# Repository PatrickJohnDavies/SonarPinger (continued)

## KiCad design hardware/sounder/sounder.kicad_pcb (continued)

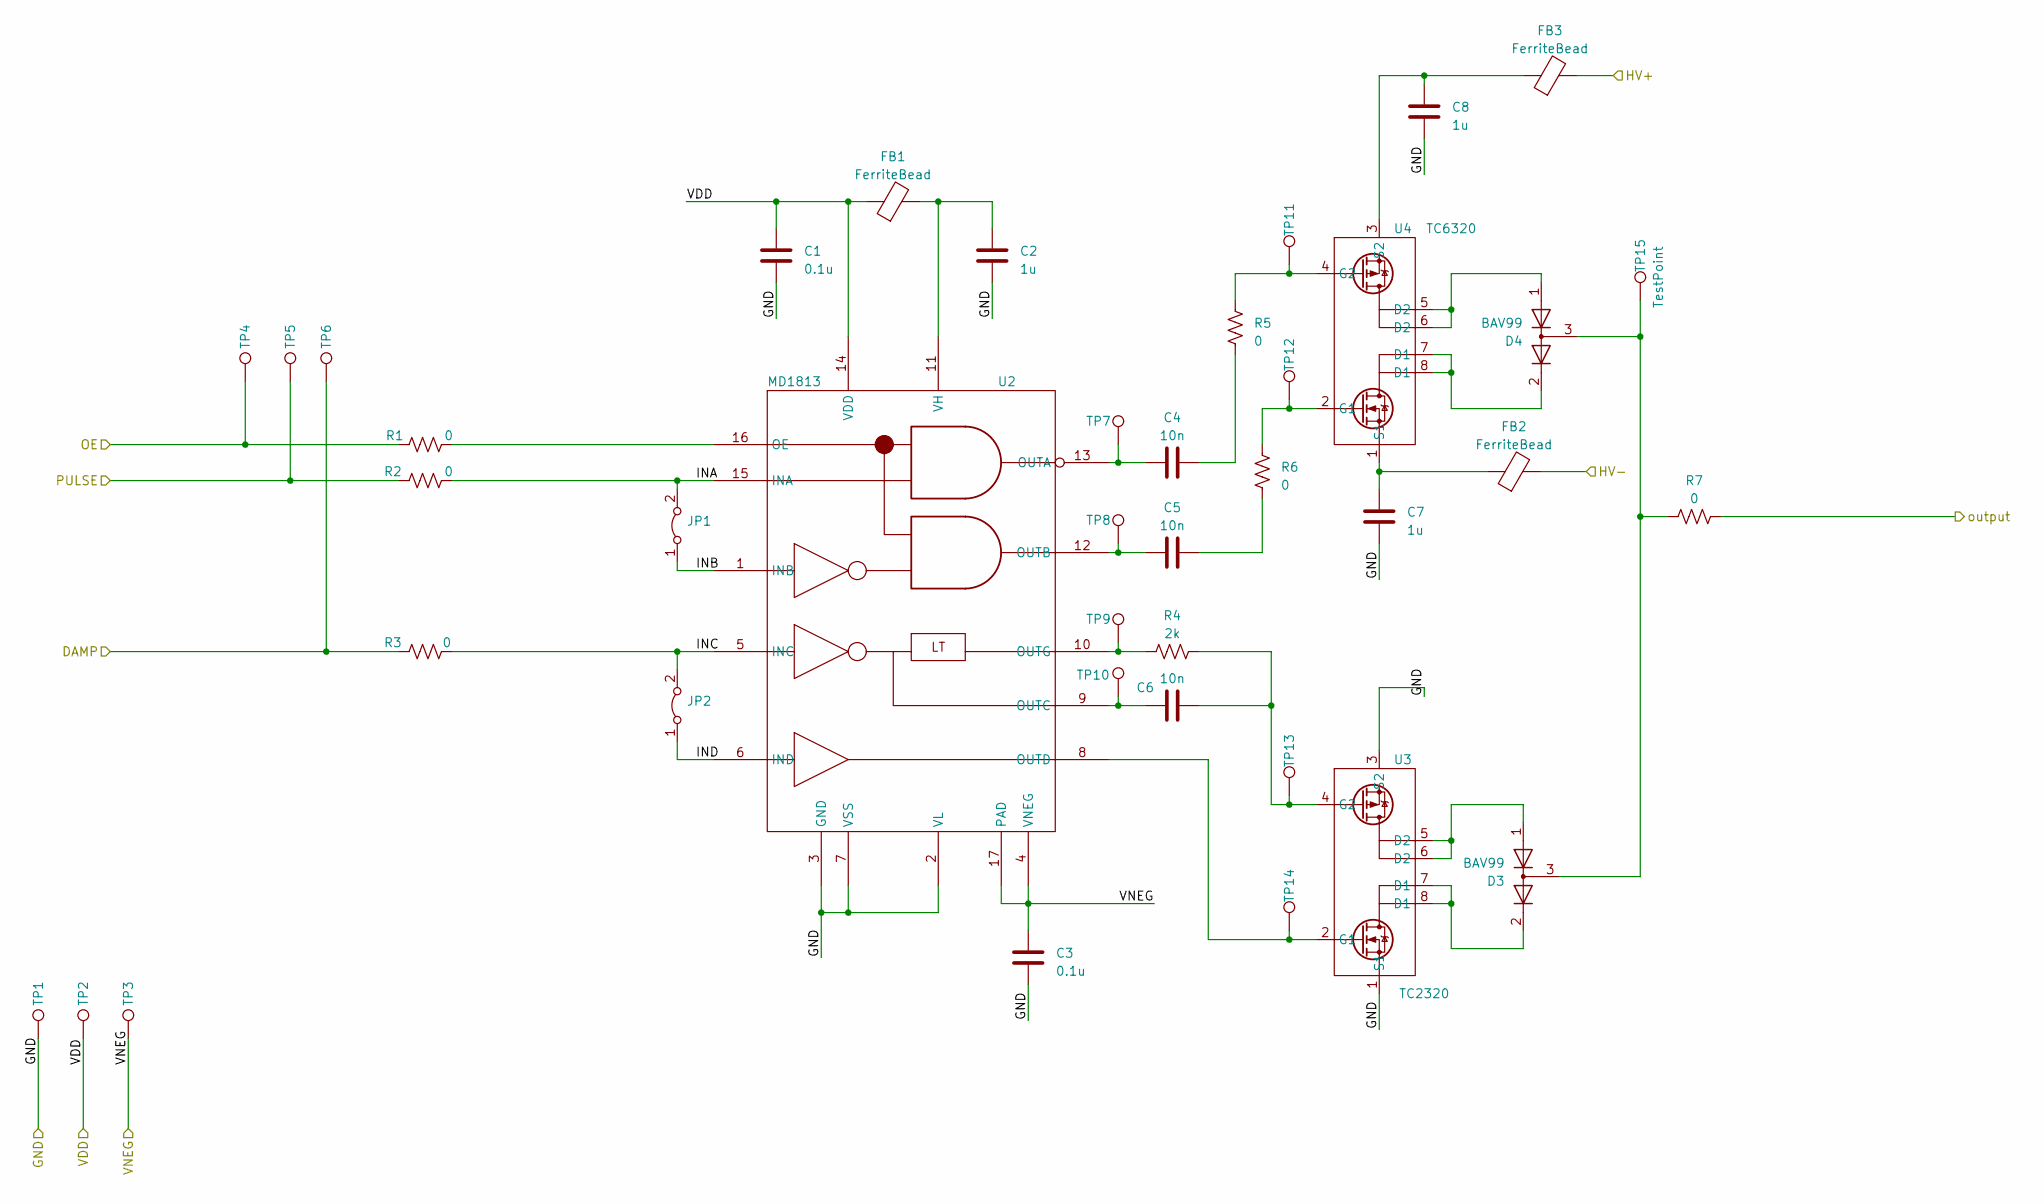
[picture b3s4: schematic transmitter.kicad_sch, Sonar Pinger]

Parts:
C1, C3: 0.1u; C_0603_1608Metric
C2: 1u; C_0201_0603Metric
C4, C5, C6: 10n; C_0603_1608Metric
C7, C8: 1u; C_1812_4532Metric
D3, D4: BAV99; SOT-23
FB1, FB2, FB3: FerriteBead; L_0603_1608Metric
JP1, JP2: Jumper_2_Bridged; SolderJumper-2_P1.3mm_Bridged_RoundedPad1.0x1.5mm
R1, R2, R3, R5, R6, R7: 0; R_0603_1608Metric
R4: 2k; R_0603_1608Metric
TP1, TP2, TP3, TP4, TP5, TP6, TP7, TP8, TP9, TP10, TP11, TP12, TP13, TP14, TP15: TestPoint; TestPoint_THTPad_D1.8mm_Drill1.2mm
U2: MD1813; QFN-16-1EP_4x4mm_P0.65mm_EP2.5x2.5mm
U3: TC2320; SOIC-8_3.9x4.9mm_P1.27mm
U4: TC6320; SOIC-8_3.9x4.9mm_P1.27mm

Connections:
/9V: C1.2, FB1.1, TP2.1, U2.14 (VDD); also elsewhere on the board
/100V: FB3.2; also elsewhere on the board
/-9V: C3.2, TP3.1, U2.4 (VNEG), U2.17 (PAD); also elsewhere on the board
/-100V: FB2.2; also elsewhere on the board
/DAMP: R3.1, TP6.1; also elsewhere on the board
/OE: R1.1, TP4.1; also elsewhere on the board
/PULSE: R2.1, TP5.1; also elsewhere on the board
/receiver/input: R7.2; also elsewhere on the board
/transmitter/INA: JP1.2 (B), R2.2, U2.15 (INA)
/transmitter/INB: JP1.1 (A), U2.1 (INB)
/transmitter/INC: JP2.2 (B), R3.2, U2.5 (INC)
/transmitter/IND: JP2.1 (A), U2.6 (IND)
GND: C1.1, C2.1, C3.1, C7.1, C8.1, TP1.1, U2.2 (VL), U2.3 (GND), U2.7 (VSS), U3.1 (S1), U3.3 (S2); also elsewhere on the board
unnamed: C4.2, R5.1
unnamed: C5.2, R6.1
unnamed: D3.2 (A), U3.7 (D1), U3.8 (D1)
unnamed: D3.1 (K), U3.5 (D2), U3.6 (D2)
unnamed: D3.3 (K), D4.3 (K), R7.1, TP15.1
unnamed: D4.2 (A), U4.7 (D1), U4.8 (D1)
unnamed: D4.1 (K), U4.5 (D2), U4.6 (D2)
unnamed: R1.2, U2.16 (OE)
unnamed: C4.1, TP7.1, U2.13 (OUTA)
unnamed: C5.1, TP8.1, U2.12 (OUTB)
unnamed: C6.1, TP10.1, U2.9 (OUTC)
unnamed: TP14.1, U2.8 (OUTD), U3.2 (G1)
unnamed: R4.1, TP9.1, U2.10 (OUTG)
unnamed: C2.2, FB1.2, U2.11 (VH)
unnamed: C6.2, R4.2, TP13.1, U3.4 (G2)
unnamed: R6.2, TP12.1, U4.2 (G1)
unnamed: R5.2, TP11.1, U4.4 (G2)
unnamed: C7.2, FB2.1, U4.1 (S1)
unnamed: C8.2, FB3.1, U4.3 (S2)

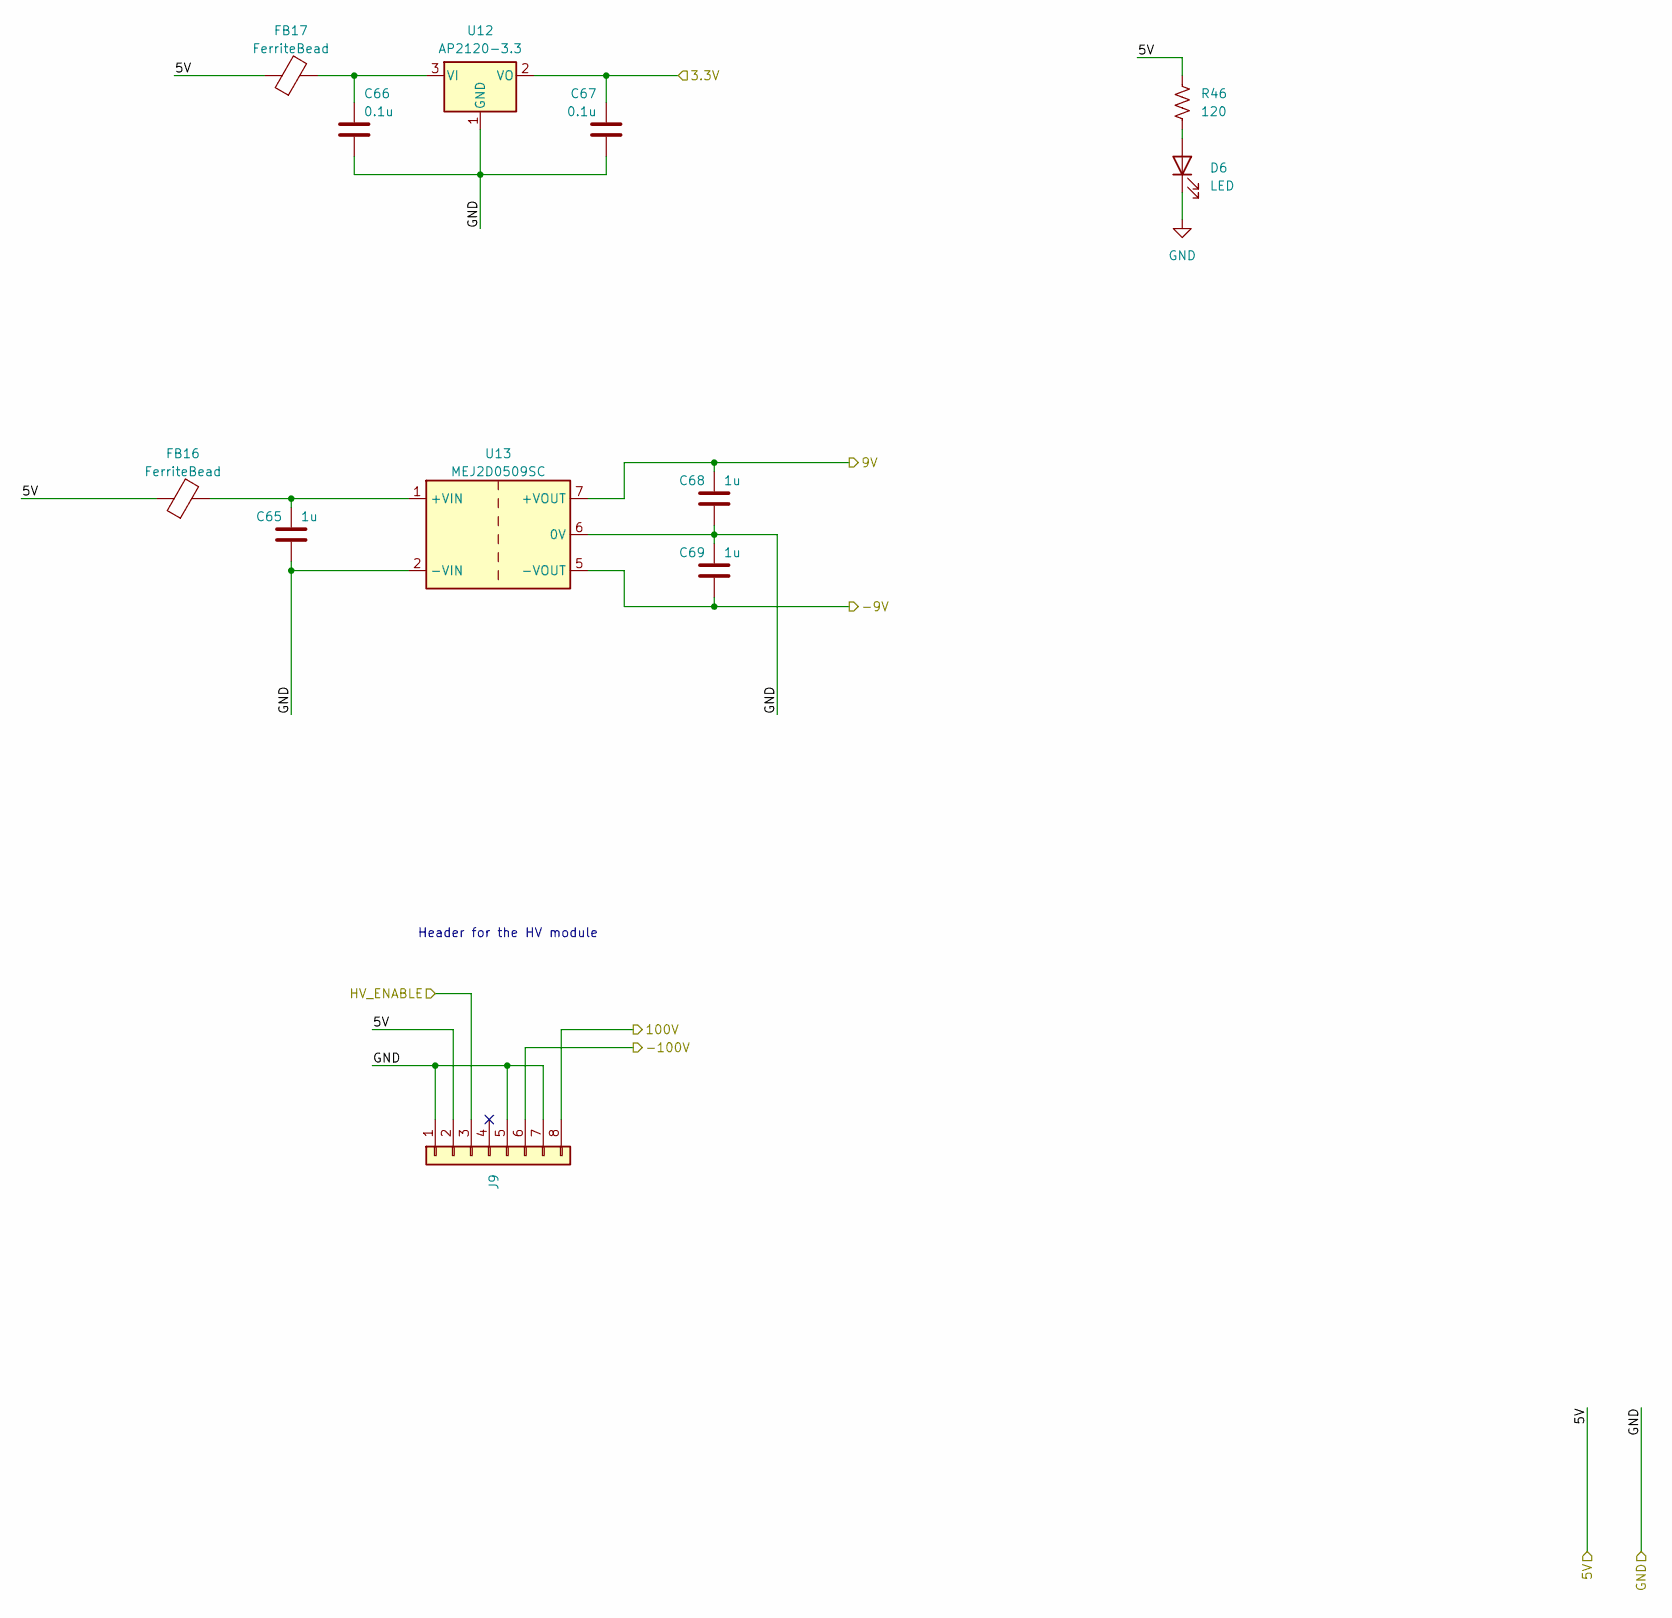
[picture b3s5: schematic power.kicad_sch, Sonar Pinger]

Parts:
C65, C68, C69: 1u; C_0603_1608Metric
C66, C67: 0.1u; C_0603_1608Metric
D6: LED; LED_1206_3216Metric_Pad1.42x1.75mm_HandSolder
FB16, FB17: FerriteBead; L_0603_1608Metric
J9: Conn_01x08; JST_PH_B8B-PH-K_1x08_P2.00mm_Vertical
R46: 120; R_0603_1608Metric
U12: AP2120-3.3; SOT-23
U13: MEJ2D0509SC; Converter_DCDC_Murata_MGJ2DxxxxxxSC_THT

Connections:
+5V: FB16.1, FB17.1, J9.2, R46.2; also elsewhere on the board
/3.3V: C67.1, U12.2 (VO); also elsewhere on the board
/9V: C68.1, U13.7 (+VOUT); also elsewhere on the board
/100V: J9.8; also elsewhere on the board
/-9V: C69.2, U13.5 (-VOUT); also elsewhere on the board
/-100V: J9.6; also elsewhere on the board
/HV_ENABLE: J9.3; also elsewhere on the board
GND: C65.2, C66.2, C67.2, C68.2, C69.1, D6.1 (K), J9.1, J9.5, J9.7, U12.1 (GND), U13.2 (-VIN), U13.6 (0V); also elsewhere on the board
unnamed: D6.2 (A), R46.1
unnamed: C66.1, FB17.2, U12.3 (VI)
unnamed: C65.1, FB16.2, U13.1 (+VIN)

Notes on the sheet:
Header for the HV module

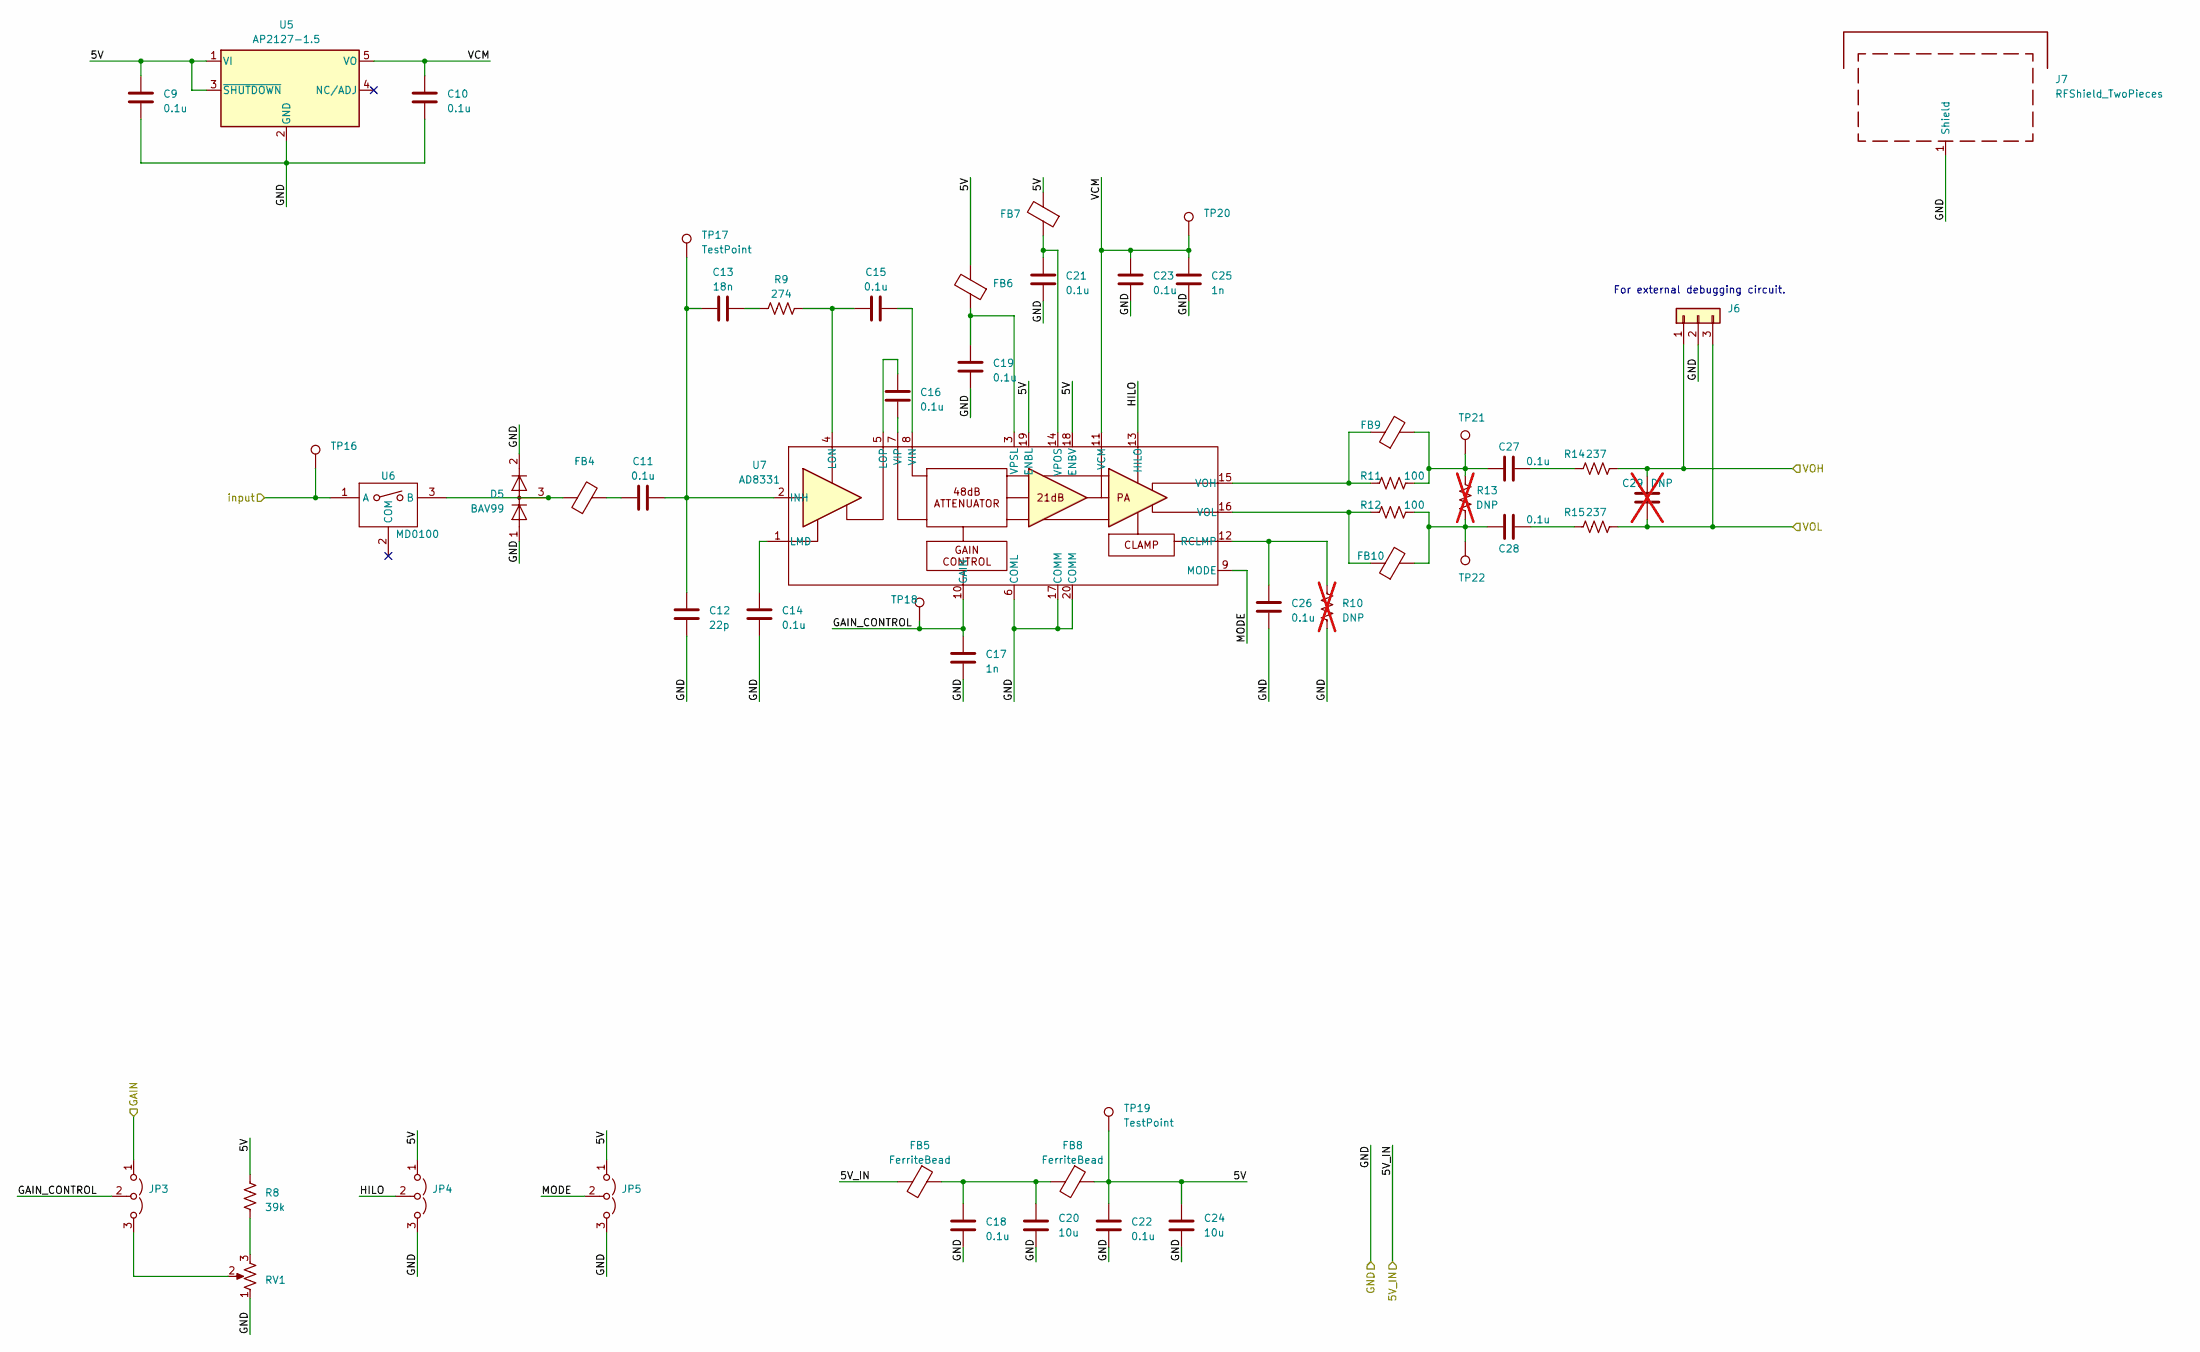
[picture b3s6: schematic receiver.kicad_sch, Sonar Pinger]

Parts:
C9, C10, C11, C14, C15, C16, C18, C19, C21, C22, C23, C26, C27, C28: 0.1u; C_0603_1608Metric
C12: 22p; C_0603_1608Metric
C13: 18n; C_0603_1608Metric
C17, C25: 1n; C_0603_1608Metric
C20, C24: 10u; C_0805_2012Metric_Pad1.18x1.45mm_HandSolder
C29: DNP; C_0603_1608Metric; not fitted
D5: BAV99; SOT-23
FB4, FB5, FB6, FB7, FB8, FB9, FB10: FerriteBead; L_0603_1608Metric
J6: Conn_01x03; PinSocket_1x03_P2.54mm_Vertical
J7: RFShield_TwoPieces; Shield_MS384-10F
JP3, JP4, JP5: Jumper_3_Open; PinHeader_1x03_P2.54mm_Vertical
R8: 39k; R_0603_1608Metric
R9: 274; R_0603_1608Metric
R10, R13: DNP; R_0603_1608Metric; not fitted
R11, R12: 100; R_0603_1608Metric
R14, R15: 237; R_0603_1608Metric
RV1: R_Potentiometer_US; Potentiometer_Bourns_3362U_Vertical
TP16, TP17, TP18, TP19, TP20, TP21, TP22: TestPoint; TestPoint_THTPad_D1.8mm_Drill1.2mm
U5: AP2127-1.5; SOT-23-5
U6: MD0100; SOT-89-3
U7: AD8331; QSOP-20_3.9x8.7mm_P0.635mm

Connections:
+5V: FB5.2; also elsewhere on the board
/adc/VIN+: C29.2, J6.1, R14.1; also elsewhere on the board
/adc/VIN-: C29.1, J6.3, R15.1; also elsewhere on the board
/dac/VOUT: JP3.1 (A); also elsewhere on the board
/receiver/5V: C9.1, C22.1, C24.1, FB6.2, FB7.2, FB8.1, JP4.1 (A), JP5.1 (A), R8.2, TP19.1, U5.1 (VI), U5.3 (~SHUTDOWN), U7.18 (ENBV), U7.19 (ENBL)
/receiver/GAIN_CONTROL: C17.1, JP3.2 (C), TP18.1, U7.10 (GAIN)
/receiver/HILO: JP4.2 (C), U7.13 (HILO)
/receiver/MODE: JP5.2 (C), U7.9 (MODE)
/receiver/VCM: C10.1, C23.1, C25.1, TP20.1, U5.5 (VO), U7.11 (VCM)
/receiver/input: TP16.1, U6.1 (A); also elsewhere on the board
GND: C9.2, C10.2, C12.2, C14.2, C17.2, C18.2, C19.2, C20.2, C21.2, C22.2, C23.2, C24.2, C25.2, C26.2, D5.1 (K), D5.2 (A), J6.2, J7.1 (Shield), JP4.3 (B), JP5.3 (B), R10.1, RV1.1, U5.2 (GND), U7.6 (COML), U7.17 (COMM), U7.20 (COMM); also elsewhere on the board
unnamed: C11.1, FB4.2
unnamed: C13.2, R9.1
unnamed: C18.1, C20.1, FB5.1, FB8.2
unnamed: C27.1, FB9.2, R11.1, R13.1, TP21.1
unnamed: C27.2, R14.2
unnamed: C28.1, FB10.2, R12.1, R13.2, TP22.1
unnamed: C28.2, R15.2
unnamed: JP3.3 (B), RV1.2
unnamed: R8.1, RV1.3
unnamed: D5.3 (K), FB4.1, U6.3 (B)
unnamed: C11.2, C12.1, C13.1, TP17.1, U7.2 (INH)
unnamed: C14.1, U7.1 (LMD)
unnamed: C15.1, R9.2, U7.4 (LON)
unnamed: C16.1, U7.5 (LOP)
unnamed: C26.1, R10.2, U7.12 (RCLMP)
unnamed: C15.2, U7.8 (VIN)
unnamed: C16.2, U7.7 (VIP)
unnamed: FB9.1, R11.2, U7.15 (VOH)
unnamed: FB10.1, R12.2, U7.16 (VOL)
unnamed: C21.1, FB7.1, U7.14 (VPOS)
unnamed: C19.1, FB6.1, U7.3 (VPSL)

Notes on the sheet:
For external debugging circuit.

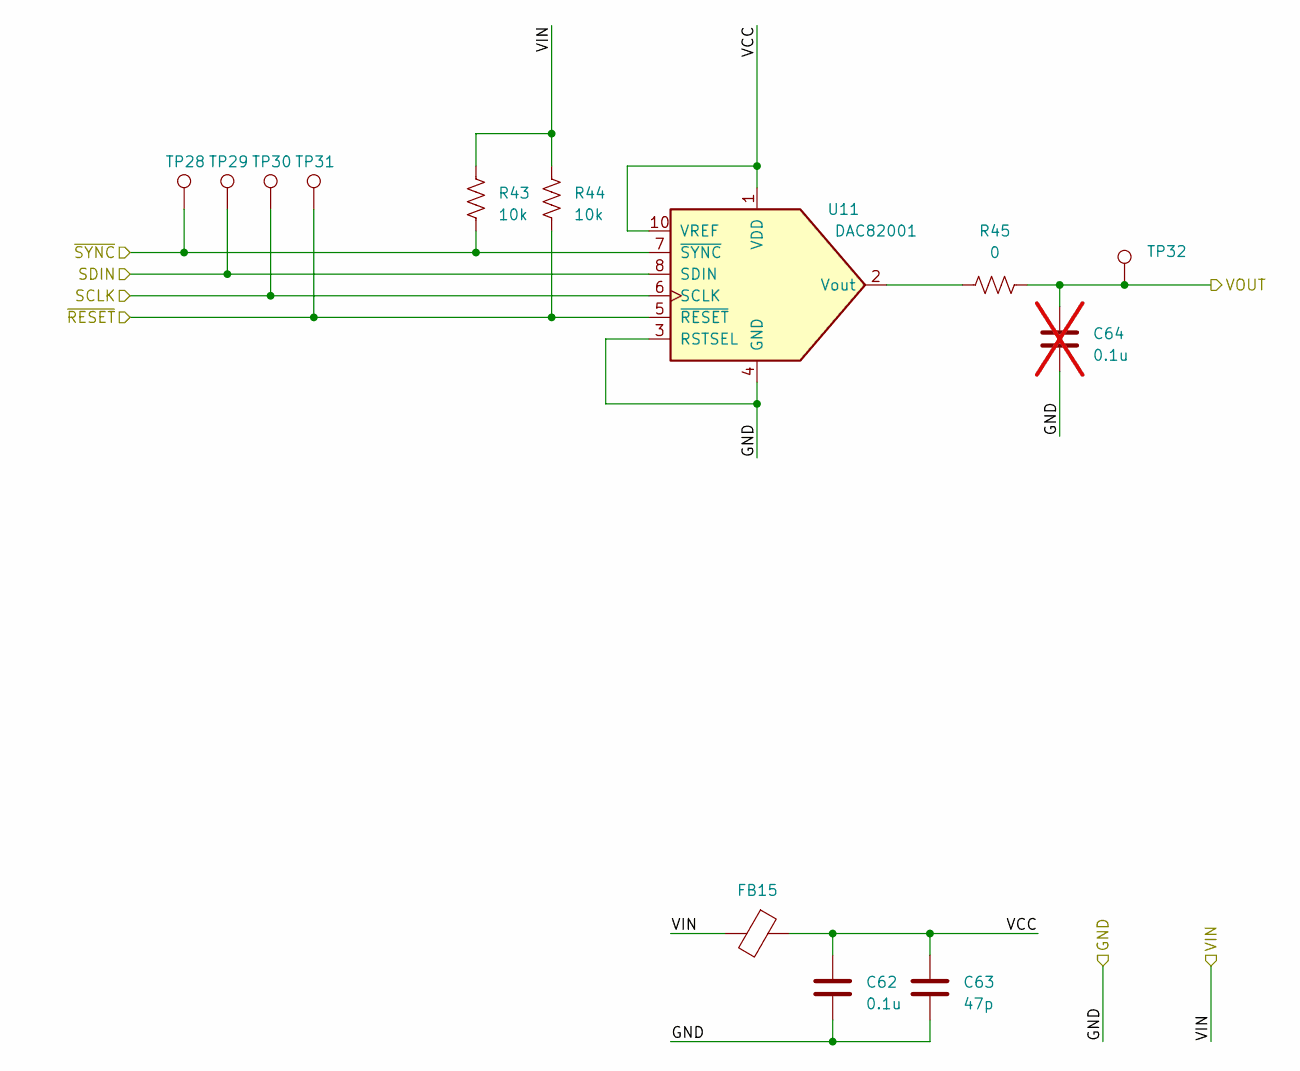
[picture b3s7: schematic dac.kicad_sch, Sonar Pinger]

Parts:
C62: 0.1u; C_0603_1608Metric
C63: 47p; C_0603_1608Metric
C64: 0.1u; C_0603_1608Metric; not fitted
FB15: FerriteBead; L_0603_1608Metric
R43, R44: 10k; R_0603_1608Metric
R45: 0; R_0603_1608Metric
TP28, TP29, TP30, TP31, TP32: TestPoint; TestPoint_THTPad_D1.8mm_Drill1.2mm
U11: DAC82001; WSON-10-2.5x2.5mm_P0.5mm

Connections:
+5V: FB15.2, R43.1, R44.1; also elsewhere on the board
/DAC_~CS: R43.2, TP28.1, U11.7 (~SYNC); also elsewhere on the board
/DAC_~RESET: R44.2, TP31.1, U11.5 (~RESET); also elsewhere on the board
/MOSI: TP29.1, U11.8 (SDIN); also elsewhere on the board
/SCLK: TP30.1, U11.6 (SCLK); also elsewhere on the board
/dac/VCC: C62.2, C63.2, FB15.1, U11.1 (VDD), U11.10 (VREF)
/dac/VOUT: C64.2, R45.2, TP32.1; also elsewhere on the board
GND: C62.1, C63.1, C64.1, U11.3 (RSTSEL), U11.4 (GND); also elsewhere on the board
unnamed: R45.1, U11.2 (Vout)

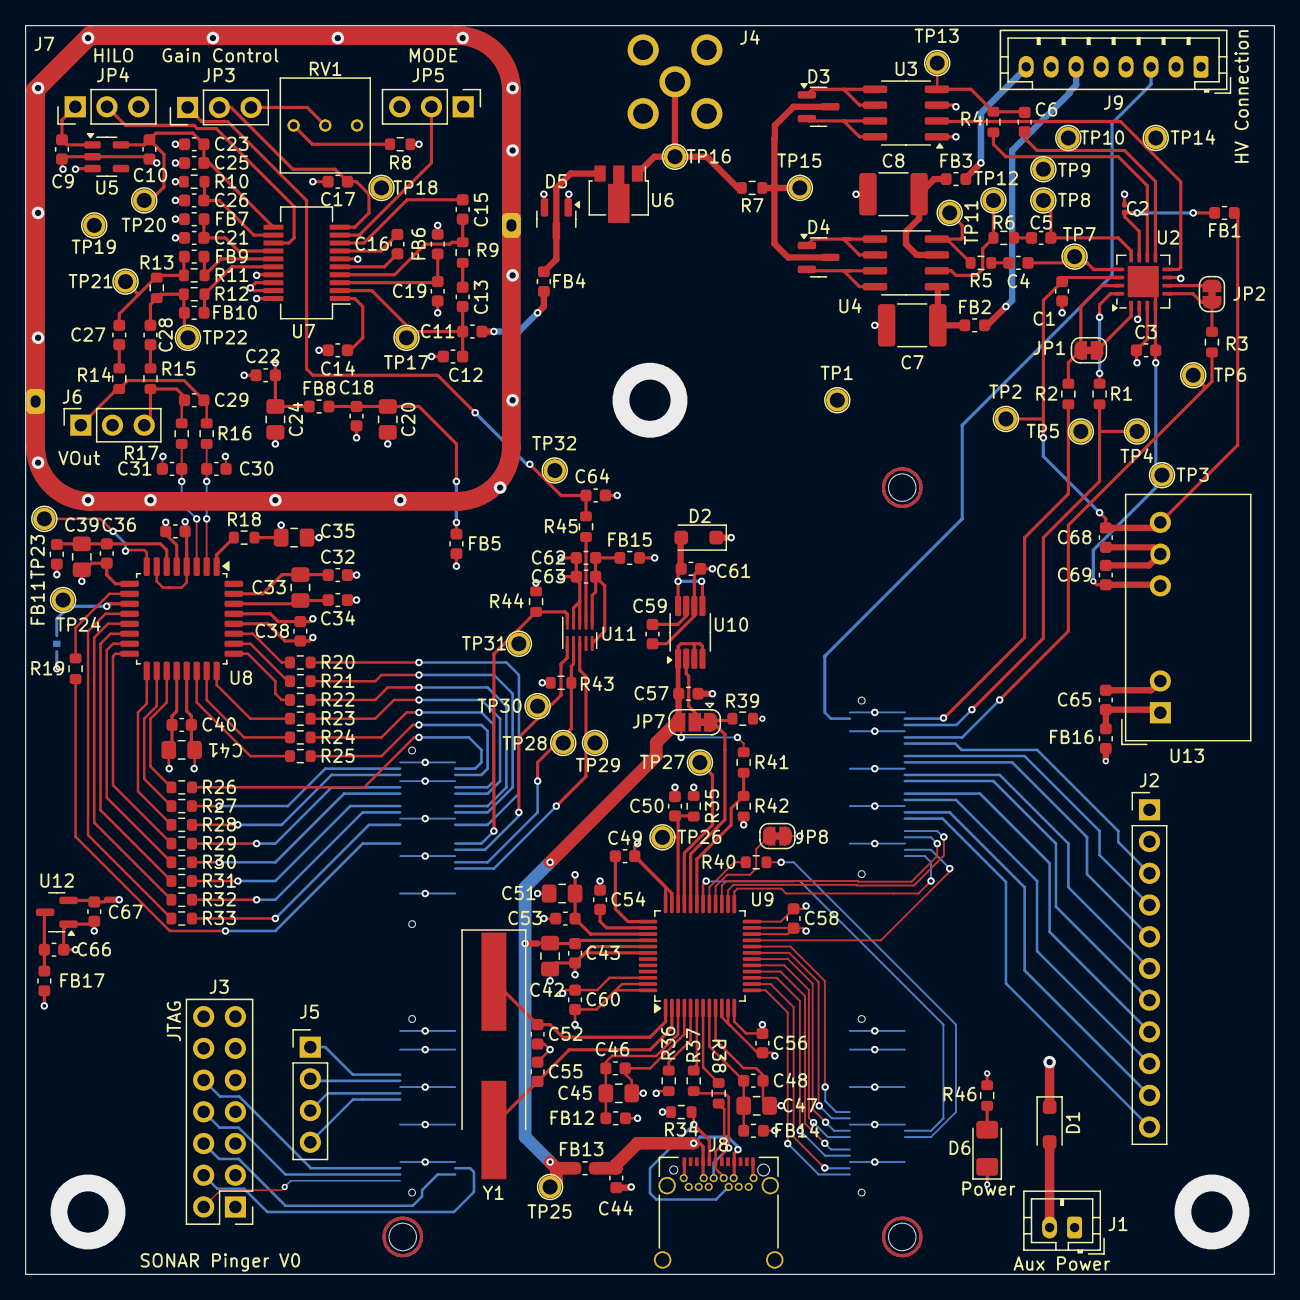
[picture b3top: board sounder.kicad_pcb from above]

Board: 4 copper layers, 100.0 x 100.0 mm, 204 parts (1 on the bottom side), 169 nets.

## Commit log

2025-05-15 Create V0 of PCBs
